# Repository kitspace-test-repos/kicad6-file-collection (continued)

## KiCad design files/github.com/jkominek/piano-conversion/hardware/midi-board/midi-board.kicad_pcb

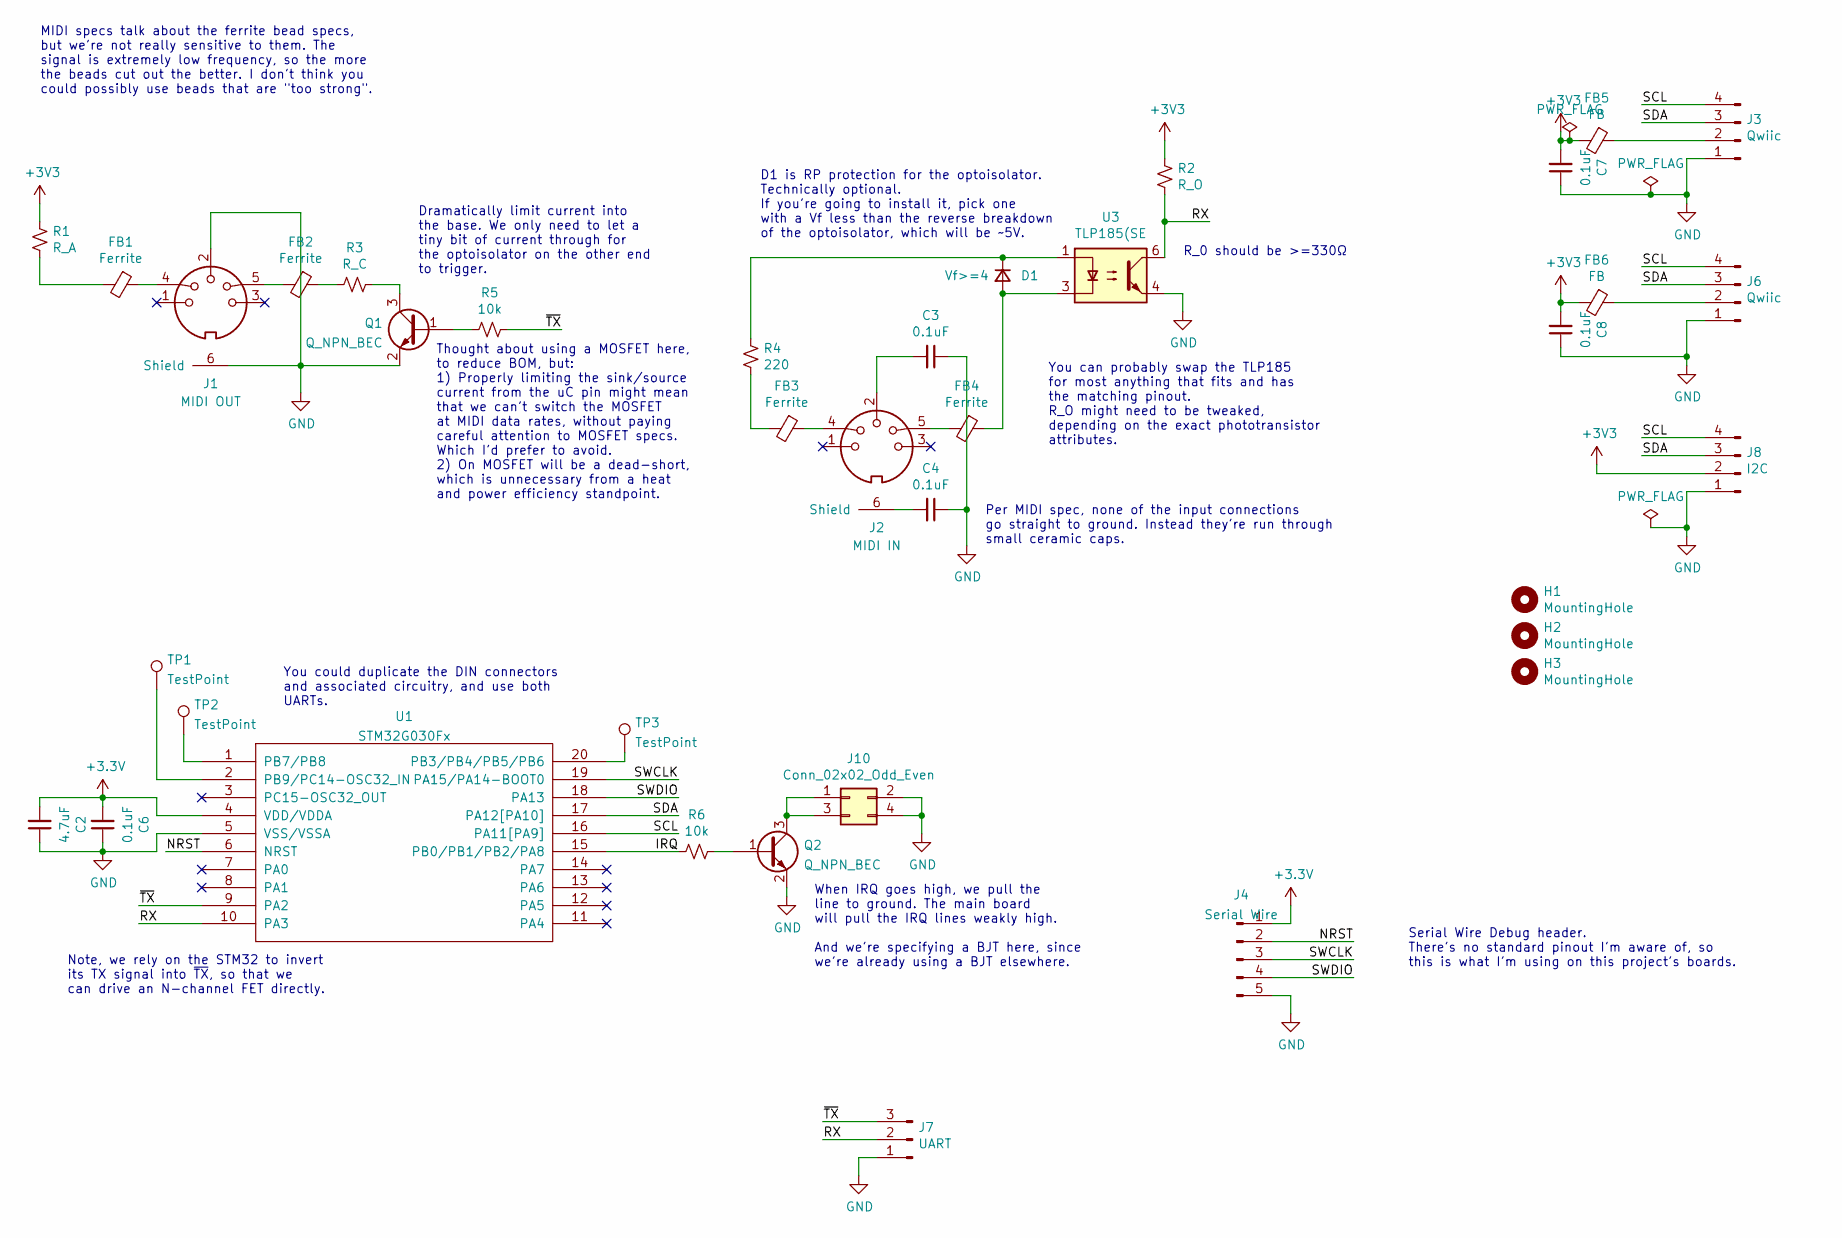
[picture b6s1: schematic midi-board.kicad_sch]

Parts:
C2: 4.7uF; C_0805_2012Metric_Pad1.18x1.45mm_HandSolder
C3, C4, C6, C7, C8: 0.1uF; C_0805_2012Metric_Pad1.18x1.45mm_HandSolder
D1: Vf>=4; D_SOD-123F
FB1, FB2, FB3, FB4: Ferrite; L_0805_2012Metric_Pad1.05x1.20mm_HandSolder
FB5, FB6: FB; L_0805_2012Metric_Pad1.05x1.20mm_HandSolder
H1, H2, H3: MountingHole; MountingHole_3.2mm_M3
J1: MIDI OUT; SDS-50J
J2: MIDI IN; SDS-50J
J3, J6: Qwiic; JST_SH_SM04B-SRSS-TB_04x1.00mm_Angled
J4: Serial Wire; PinHeader_1x05_P2.54mm_Vertical
J7: UART; Pin_Header_Straight_1x03_Pitch2.54mm
J8: I2C; Pin_Header_Straight_1x04_Pitch2.54mm
J10: Conn_02x02_Odd_Even; Pin_Header_Straight_2x02_Pitch2.54mm
Q1, Q2: Q_NPN_BEC; SOT-23
R1: R_A; R_0805_2012Metric_Pad1.20x1.40mm_HandSolder
R2: R_O; R_0805_2012Metric_Pad1.20x1.40mm_HandSolder
R3: R_C; R_0805_2012Metric_Pad1.20x1.40mm_HandSolder
R4: 220; R_0805_2012Metric_Pad1.20x1.40mm_HandSolder
R5, R6: 10k; R_0805_2012Metric_Pad1.20x1.40mm_HandSolder
TP1, TP2, TP3: TestPoint; TestPoint_Pad_D1.0mm
U1: STM32G030Fx; TSSOP-20_4.4x6.5mm_P0.65mm
U3: TLP185(SE; SO-6_4.4x3.6mm_Pitch1.27mm

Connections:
/IRQ: R6.2, U1.15 (PB0/PB1/PB2/PA8)
/NRST: J4.2, U1.6 (NRST)
/RX: J7.2, R2.2, U1.10 (PA3), U3.6
/SCL: J3.4, J6.4, J8.4, U1.16 (PA11[PA9])
/SDA: J3.3, J6.3, J8.3, U1.17 (PA12[PA10])
/SWCLK: J4.3, U1.19 (PA15/PA14-BOOT0)
/SWDIO: J4.4, U1.18 (PA13)
/~TX: J7.3, R5.1, U1.9 (PA2)
GND: C2.1, C3.1, C4.1, C6.1, C7.1, C8.1, J1.2, J1.6 (Shield), J3.1, J4.5, J6.1, J7.1, J8.1, J10.2, J10.4, Q1.2 (E), Q2.2 (E), U1.5 (VSS/VSSA), U3.4
unnamed: C3.2, J2.2
unnamed: C4.2, J2.6 (Shield)
unnamed: D1.1 (K), R4.1, U3.1
unnamed: D1.2 (A), FB4.1, U3.3
unnamed: FB1.1, J1.4
unnamed: FB1.2, R1.2
unnamed: FB2.1, R3.2
unnamed: FB2.2, J1.5
unnamed: FB3.1, J2.4
unnamed: FB3.2, R4.2
unnamed: FB4.2, J2.5
unnamed: FB5.1, J3.2
unnamed: FB6.1, J6.2
unnamed: J10.1, J10.3, Q2.3 (C)
unnamed: Q1.1 (B), R5.2
unnamed: Q1.3 (C), R3.1
unnamed: Q2.1 (B), R6.1
unnamed: TP1.1, U1.2 (PB9/PC14-OSC32_IN)
unnamed: TP2.1, U1.1 (PB7/PB8)
unnamed: TP3.1, U1.20 (PB3/PB4/PB5/PB6)

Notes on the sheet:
MIDI specs talk about the ferrite bead specs, but we're not really sensitive to them. The signal is extremely low frequency, so the more the beads cut out the better. I don't think you could possibly use beads that are "too strong".
When IRQ goes high, we pull the line to ground. The main board will pull the IRQ lines weakly high. And we're specifying a BJT here, since we're already using a BJT elsewhere.
R_0 should be >=330Ω
Per MIDI spec, none of the input connections go straight to ground. Instead they're run through small ceramic caps.
Note, we rely on the STM32 to invert its TX signal into ~{TX}, so that we can drive an N-channel FET directly.
You can probably swap the TLP185 for most anything that fits and has the matching pinout. R_O might need to be tweaked, depending on the exact phototransistor attributes.
Thought about using a MOSFET here, to reduce BOM, but: 1) Properly limiting the sink/source current from the uC pin might mean that we can't switch the MOSFET at MIDI data rates, without paying careful attention to MOSFET specs. Which I'd prefer to avoid. 2) On MOSFET will be a dead-short, which is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
Serial Wire Debug header. There's no standard pinout I'm aware of, so this is what I'm using on this project's boards.
D1 is RP protection for the optoisolator. Technically optional. If you're going to install it, pick one with a Vf less than the reverse breakdown of the optoisolator, which will be ~5V.
Dramatically limit current into the base. We only need to let a tiny bit of current through for the optoisolator on the other end to trigger.
You could duplicate the DIN connectors and associated circuitry, and use both UARTs.

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
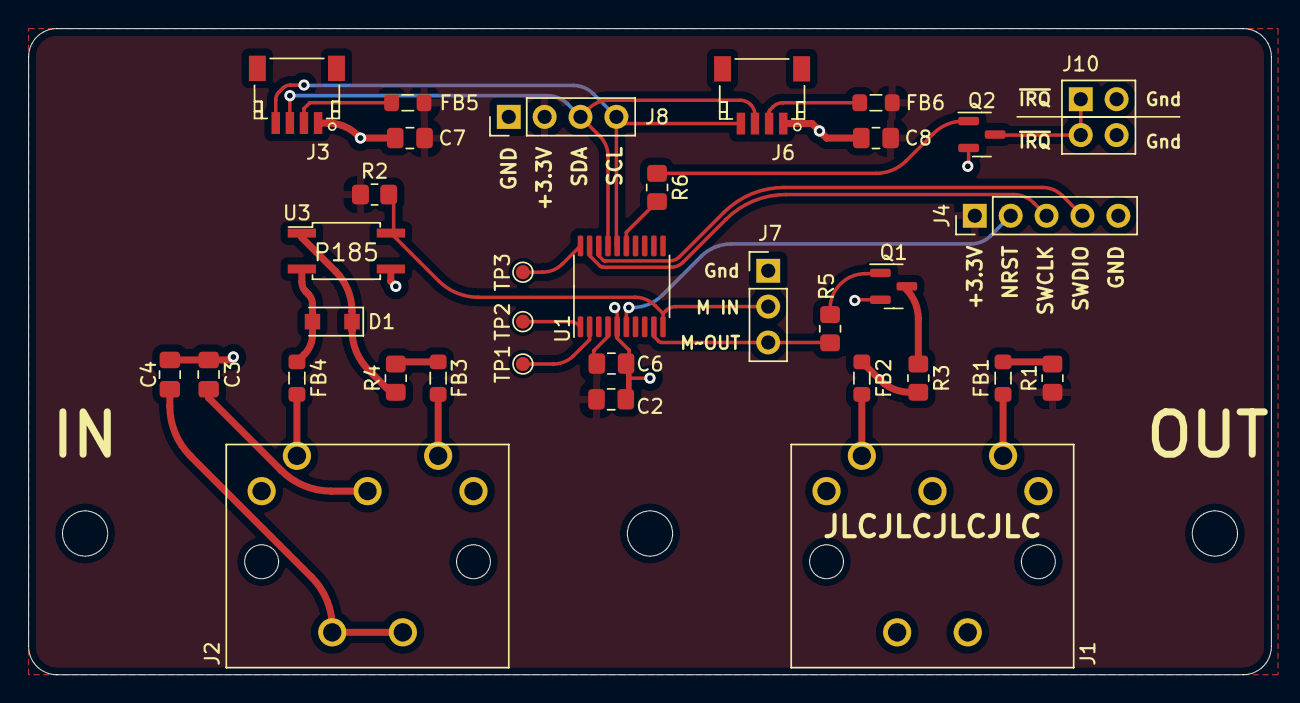
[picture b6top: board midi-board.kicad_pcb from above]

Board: 2 copper layers, 88.0 x 45.8 mm, 37 parts (0 on the bottom side), 30 nets.

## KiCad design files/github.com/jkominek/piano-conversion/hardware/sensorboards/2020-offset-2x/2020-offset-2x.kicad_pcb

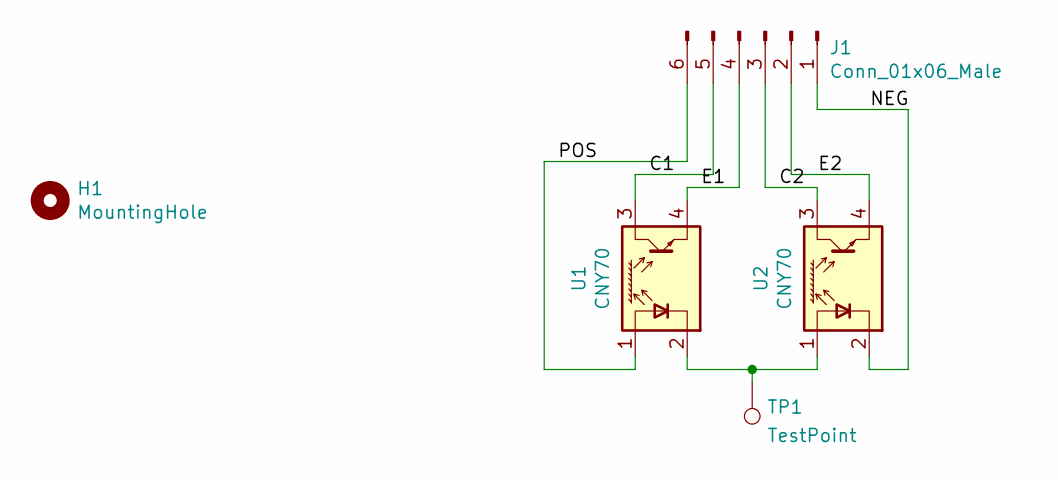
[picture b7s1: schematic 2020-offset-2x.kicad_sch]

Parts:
H1: MountingHole; MountingHole_3.2mm_M3
J1: Conn_01x06_Male; Pin_Header_Angled_1x06_Pitch2.54mm
TP1: TestPoint; TestPoint_Pad_1.0x1.0mm
U1, U2: CNY70; Vishay_CNY70

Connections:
/C1: J1.5, U1.3 (C)
/C2: J1.3, U2.3 (C)
/E1: J1.4, U1.4 (E)
/E2: J1.2, U2.4 (E)
/NEG: J1.1, U2.2 (K)
/POS: J1.6, U1.1 (A)
unnamed: TP1.1, U1.2 (K), U2.1 (A)

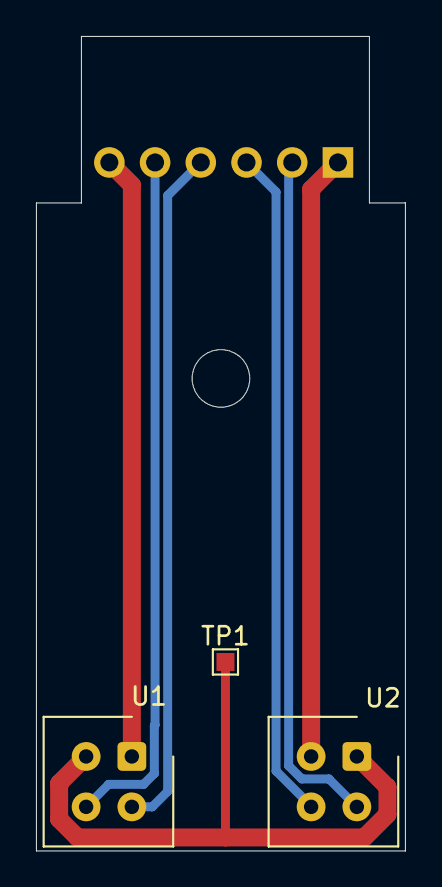
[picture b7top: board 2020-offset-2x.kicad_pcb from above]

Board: 2 copper layers, 20.5 x 45.2 mm, 5 parts (1 on the bottom side), 7 nets.

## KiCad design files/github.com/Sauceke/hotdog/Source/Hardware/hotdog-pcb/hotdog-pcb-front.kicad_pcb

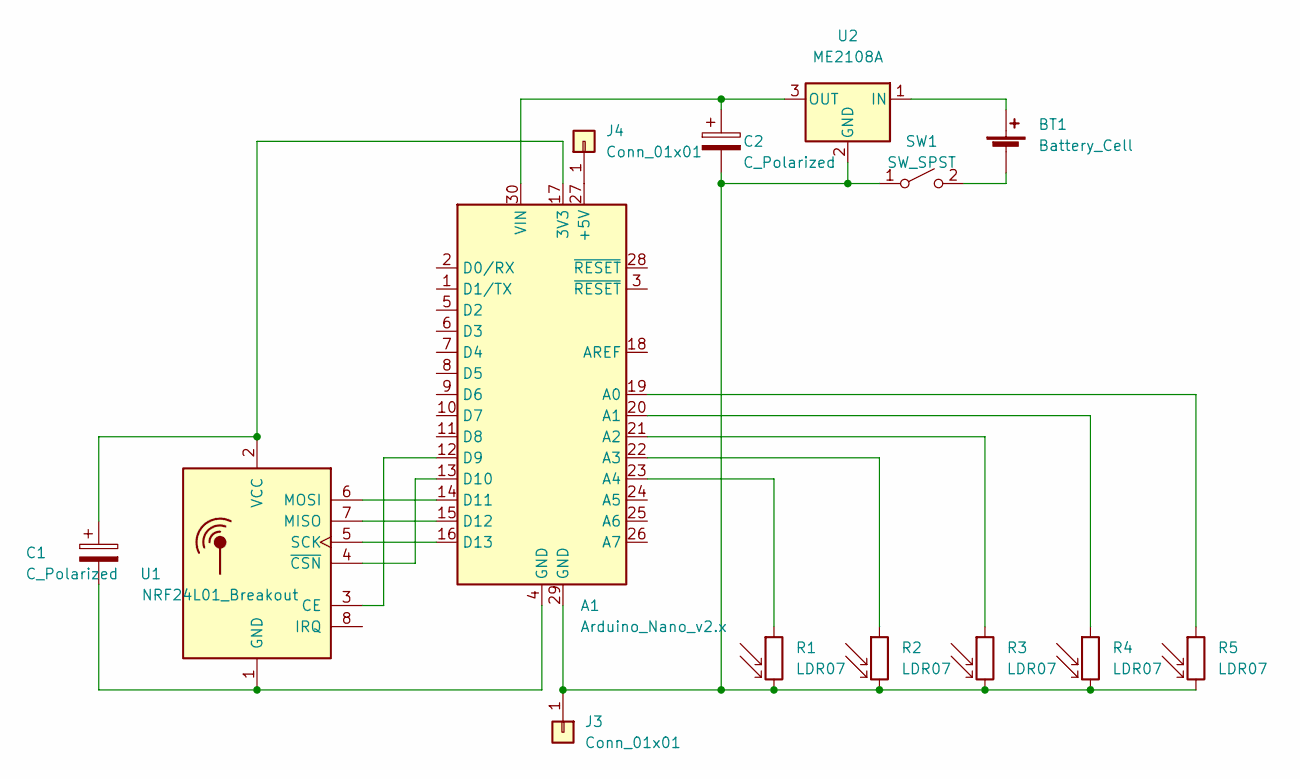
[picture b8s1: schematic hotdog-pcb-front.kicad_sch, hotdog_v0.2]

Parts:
A1: Arduino_Nano_v2.x; Arduino_Nano
BT1: Battery_Cell; BatteryHolder_Keystone_2466_1xAAA
C1, C2: C_Polarized; CP_Radial_D6.3mm_P2.50mm
J3, J4: Conn_01x01; SolderWire-0.1sqmm_1x01_D0.4mm_OD1mm
R1, R2, R3, R4, R5: LDR07; R_LDR_5.1x4.3mm_P3.4mm_Vertical
SW1: SW_SPST; SW_CuK_OS102011MA1QN1_SPDT_Angled
U1: NRF24L01_Breakout; nRF24L01_Breakout
U2: ME2108A; Converter_DCDC_RECOM_R-78E-0.5_THT

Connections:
unnamed: A1.4 (GND), C1.2, U1.1 (GND)
unnamed: A1.12 (D9), U1.3 (CE)
unnamed: A1.13 (D10), U1.4 (~CSN)
unnamed: A1.14 (D11), U1.6 (MOSI)
unnamed: A1.15 (D12), U1.7 (MISO)
unnamed: A1.16 (D13), U1.5 (SCK)
unnamed: A1.17 (3V3), C1.1, U1.2 (VCC)
unnamed: A1.19 (A0), R5.1
unnamed: A1.20 (A1), R4.1
unnamed: A1.21 (A2), R3.1
unnamed: A1.22 (A3), R2.1
unnamed: A1.23 (A4), R1.1
unnamed: A1.27 (+5V), J4.1
unnamed: A1.29 (GND), C2.2, J3.1, R1.2, R2.2, R3.2, R4.2, R5.2, SW1.1 (A), U2.2 (GND)
unnamed: A1.30 (VIN), C2.1, U2.3 (OUT)
unnamed: BT1.1 (+), U2.1 (IN)
unnamed: BT1.2 (-), SW1.2 (B)

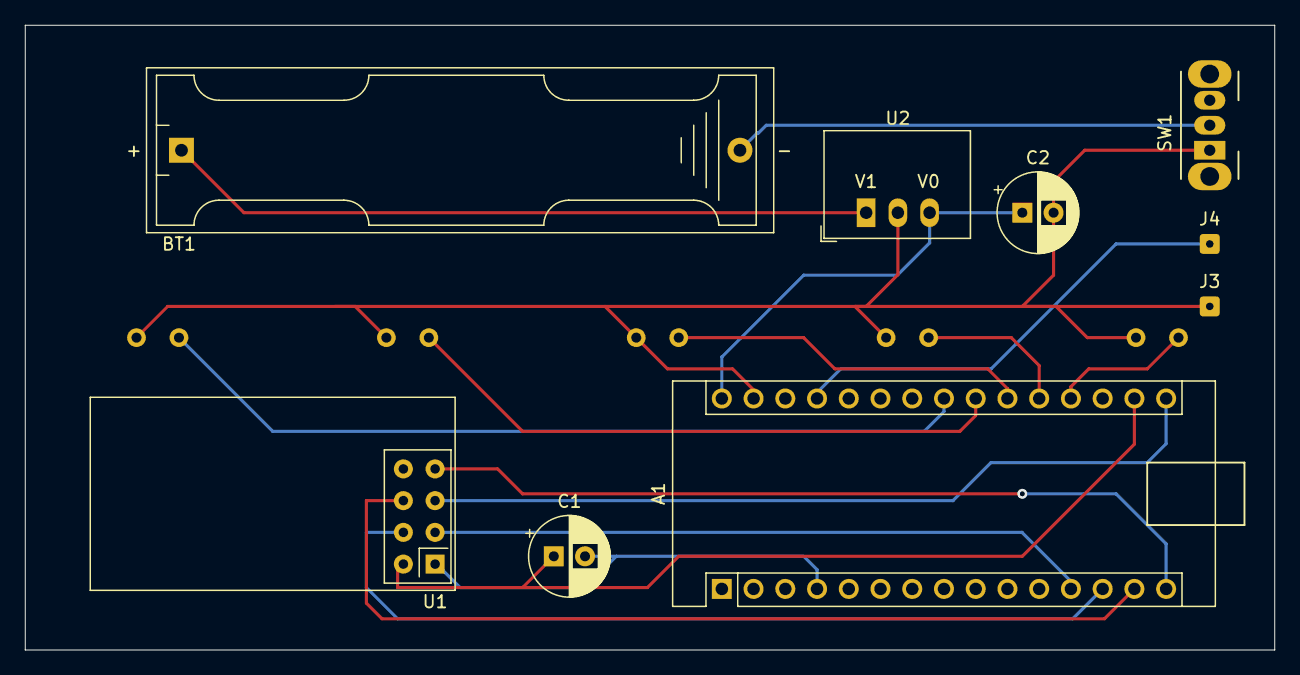
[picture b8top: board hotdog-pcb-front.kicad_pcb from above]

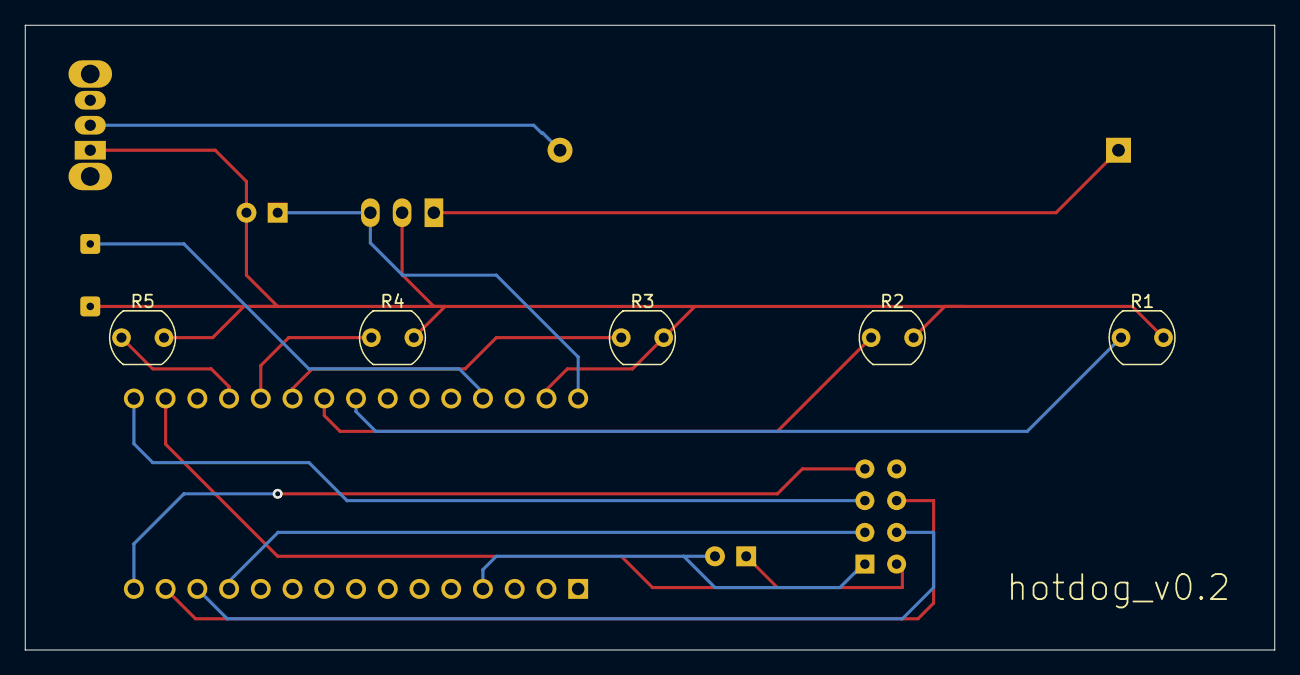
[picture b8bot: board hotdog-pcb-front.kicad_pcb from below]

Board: 2 copper layers, 100.0 x 50.0 mm, 14 parts (5 on the bottom side), 17 nets.

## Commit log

2022-08-10 Add kicad_sch files
2022-08-11 Get rid of duplicate files
2022-08-11 Add .kicad_pcb files
2022-08-11 Move kicad-source-mirror files to gitlab
2022-08-12 Add license
2022-08-12 Include .kicad_pro
2022-08-12 Refactor get_kicad6_files.py
2022-08-14 Remove muVox invalid path file names for windows
    `:` is not allows in windows paths and causes the git clone to fail.
    We'd like to us this to test for windows too.
2022-08-14 Remove another project that uses `:` in filename
2022-09-17 Remove incomplete schematic
